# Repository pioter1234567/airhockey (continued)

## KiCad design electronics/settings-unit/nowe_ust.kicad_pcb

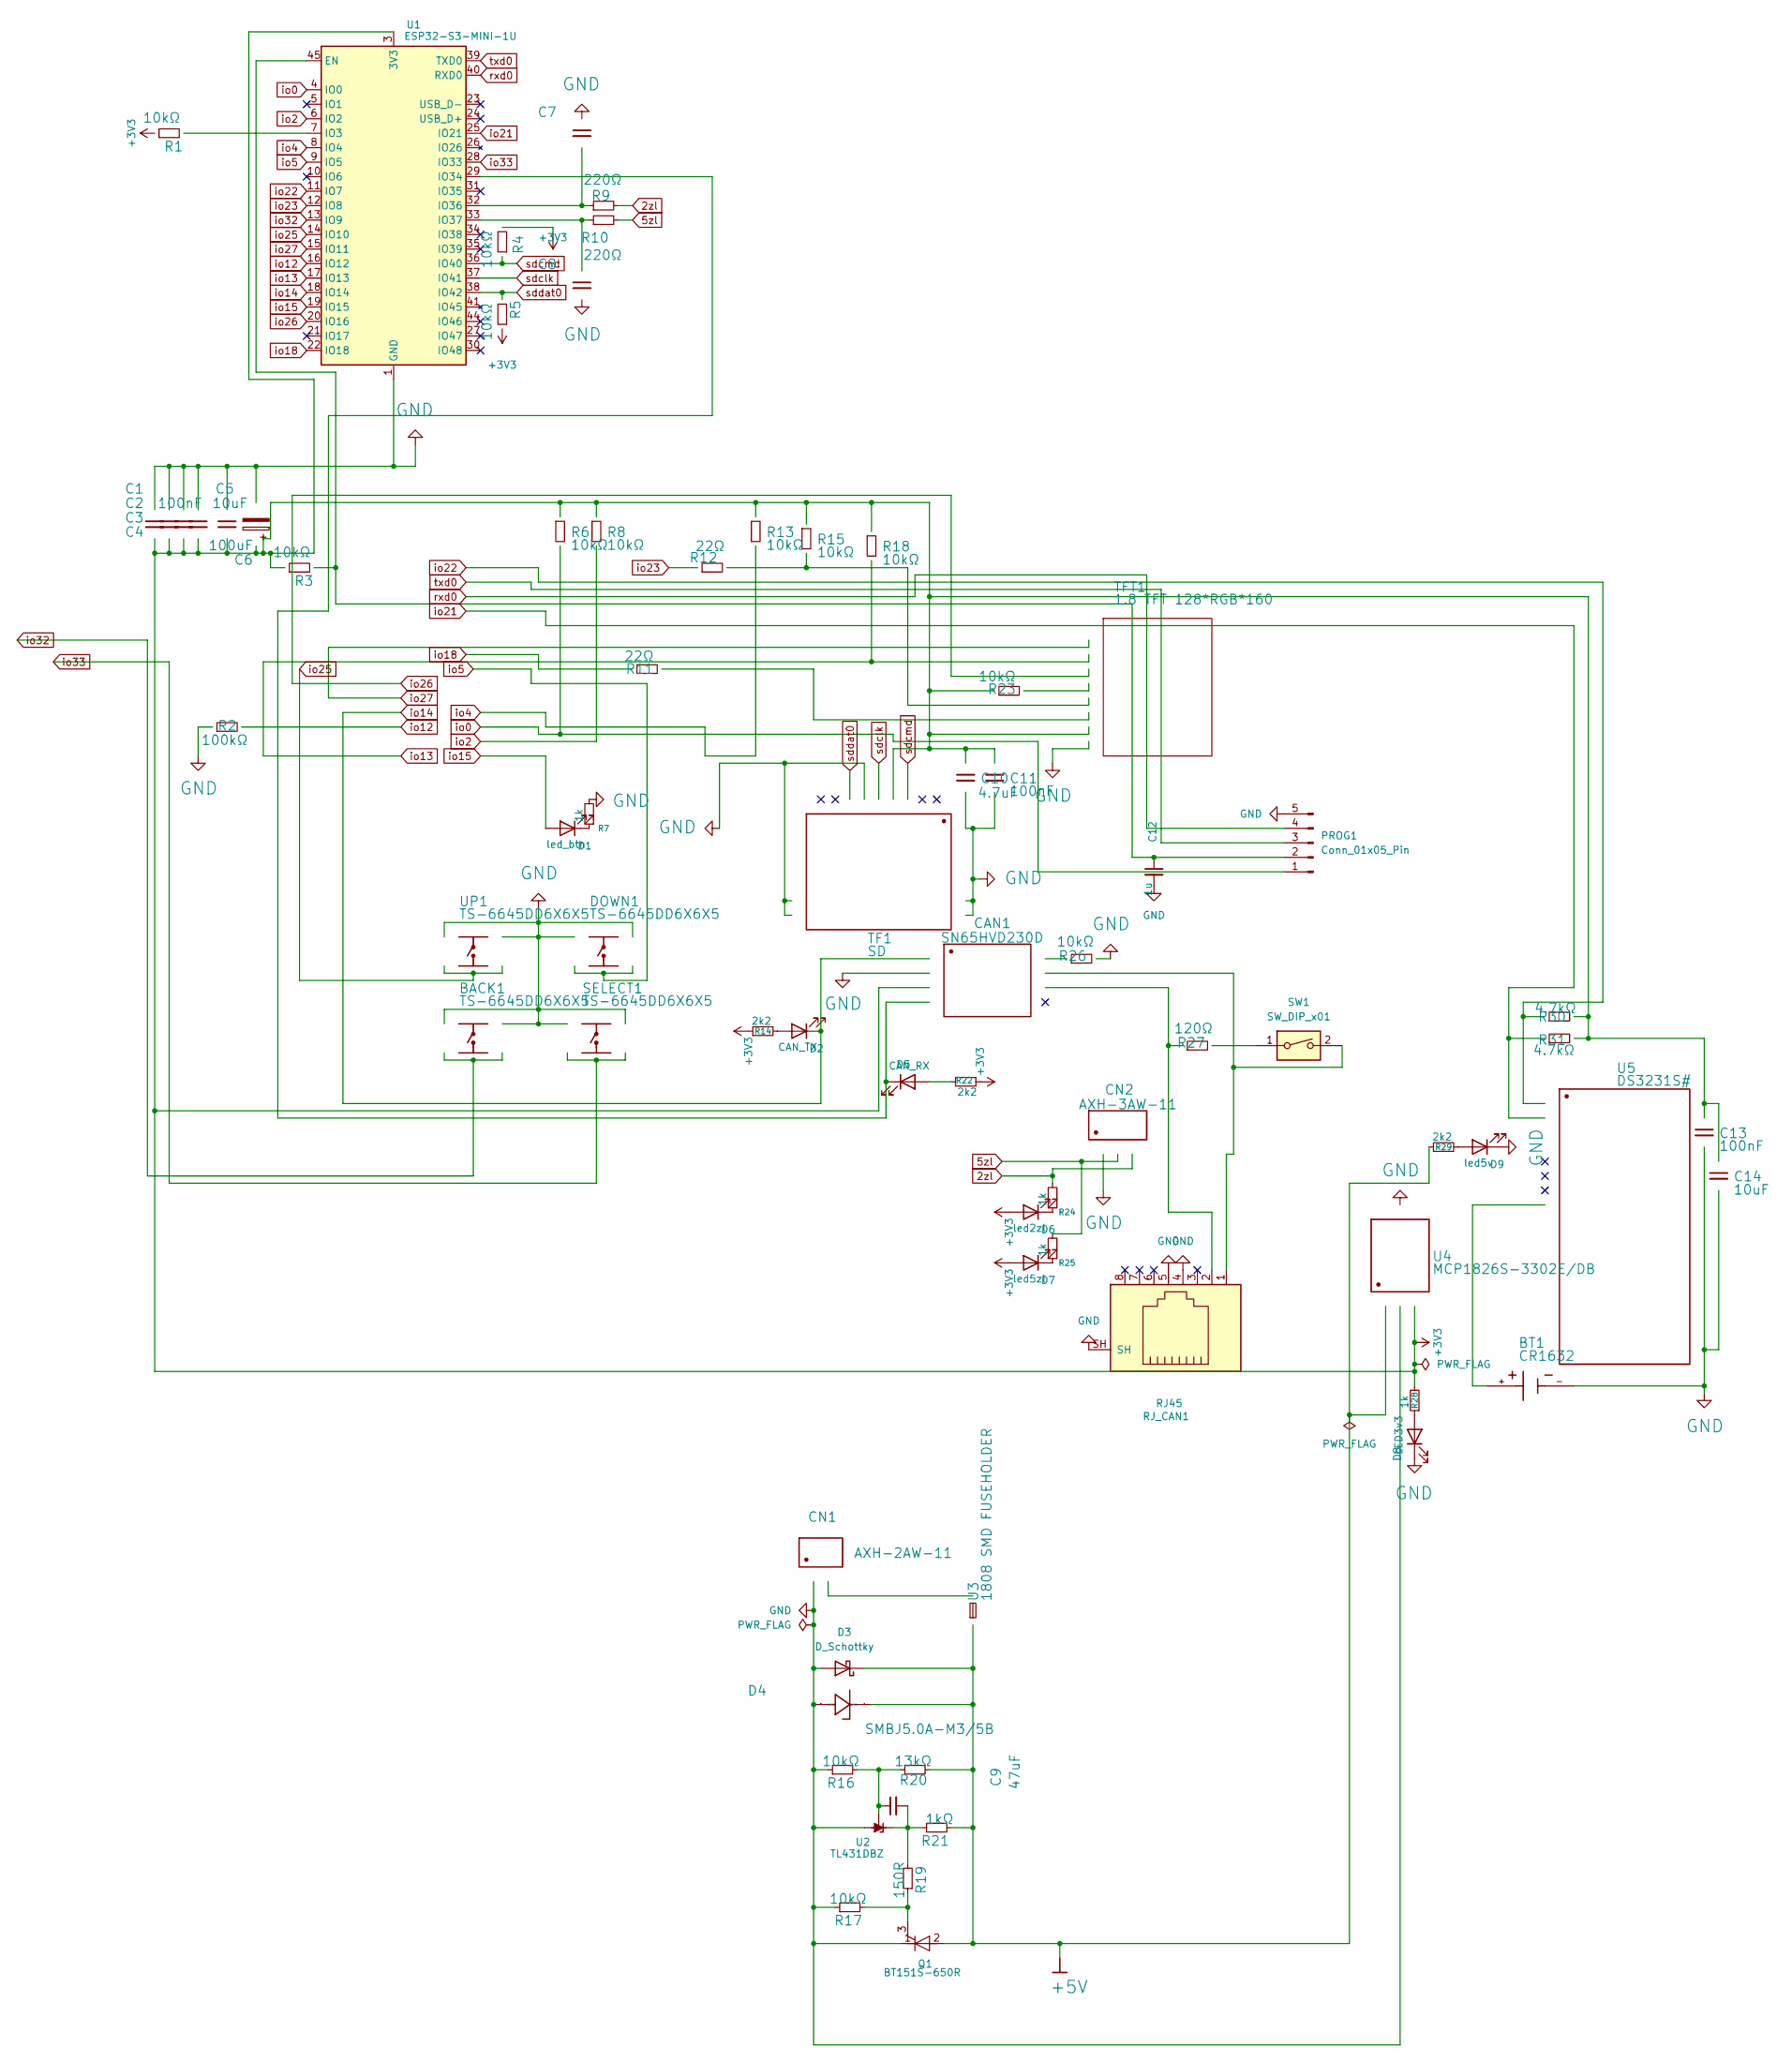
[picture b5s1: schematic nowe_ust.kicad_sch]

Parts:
BACK1: TS-6645DD6X6X5; SW_PUSH_6mm_H13mm; Manufacturer Part TS-6645DD6x6x5
BT1: CR1632; BAT_BU1632SM-JJ-GTR; Manufacturer Part XDBS-CR2032-9
C1, C2, C3, C4, C7, C8, C11, C13: 100nF; C_0805_2012Metric_Pad1.18x1.45mm_HandSolder; Manufacturer Part 0805B104K160CT-C
C5: 10uF; C_0805_2012Metric_Pad1.18x1.45mm_HandSolder; Manufacturer Part 0805ZD106KAT2A
C6: 100uF; CP_Elec_5x5.3; Manufacturer Part RVT100UF10V67RV0036
C9: 47uF; C_0805_2012Metric_Pad1.18x1.45mm_HandSolder; Manufacturer Part CGA0805X7R106K100MT
C10: 4.7uF; C_0805_2012Metric_Pad1.18x1.45mm_HandSolder; Manufacturer Part TCC0805X5R475M500FT
C12: 1u; C_0805_2012Metric
C14: 10uF; C_0805_2012Metric_Pad1.18x1.45mm_HandSolder; Manufacturer Part CGA0805X7R106K100MT
CAN1: SN65HVD230D; SOIC127P599X175-8N; Manufacturer Part SN65HVD230D
CN1: AXH-2AW-11; JST_XH_S2B-XH-A-1_1x02_P2.50mm_Horizontal; Manufacturer Part AXH-2AW-11
CN2: AXH-3AW-11; JST_PH_S3B-PH-K_1x03_P2.00mm_Horizontal; Manufacturer Part AXH-3AW-11
D1: led_btn; LED_0805_2012Metric
D2: CAN_TX; LED_0805_2012Metric
D3: D_Schottky; D_SMA
D4: SMBJ5.0A-M3/5B; D_SMB; Manufacturer Part SMBJ5.0A-M3/5B
D5: CAN_RX; LED_0805_2012Metric
D6: led2zl; LED_0805_2012Metric
D7: led5zl; LED_0805_2012Metric
D8: LED3v3; LED_0805_2012Metric
D9: led5v; LED_0805_2012Metric
DOWN1: TS-6645DD6X6X5; SW_PUSH_6mm_H13mm; Manufacturer Part TS-6645DD6x6x5
PROG1: Conn_01x05_Pin; JST_SH_BM05B-SRSS-TB_1x05-1MP_P1.00mm_Vertical
Q1: BT151S-650R; IC_BT136S-600E_118
R1, R3, R4, R5, R6, R8, R13, R15, R18: 10kΩ; R_0805_2012Metric; Manufacturer Part RCC080510K0FKEA
R2: 100kΩ; R_0805_2012Metric; Manufacturer Part APC0603B100KN
R7, R24, R25, R28: 1k; R_0805_2012Metric
R9, R10: 220Ω; R_0805_2012Metric; Manufacturer Part SC0805F22R0F4ANRH
R11, R12: 22Ω; R_0805_2012Metric; Manufacturer Part SC0805F22R0F4ANRH
R14, R22, R29: 2k2; R_0805_2012Metric
R16, R17: 10kΩ; R_0805_2012Metric; Manufacturer Part RMC08054.7K1%N
R19: 150R; R_0805_2012Metric; Manufacturer Part RMC08054.7K1%N
R20: 13kΩ; R_0805_2012Metric; Manufacturer Part RMC08054.7K1%N
R21: 1kΩ; R_0805_2012Metric; Manufacturer Part RMC08054.7K1%N
R23, R26: 10kΩ; R_0805_2012Metric; Manufacturer Part RT0603LRA0710KL
R27: 120Ω; R_0805_2012Metric; Manufacturer Part 0603SAJ0121T5E
R30, R31: 4.7kΩ; R_0805_2012Metric; Manufacturer Part RMC08054.7K1%N
RJ_CAN1: RJ45; RJ45_Amphenol_RJHSE5380
SELECT1: TS-6645DD6X6X5; SW_PUSH_6mm_H13mm; Manufacturer Part TS-6645DD6x6x5
SW1: SW_DIP_x01; SW_DIP_SPSTx01_Slide_6.7x4.1mm_W7.62mm_P2.54mm_LowProfile
TF1: SD; CUI_MSD-4-A; Manufacturer Part SD
TFT1: 1.8 TFT 128*RGB*160; TFT 1.8 No card No touch; Manufacturer Part 1.8 TFT 128*RGB*160
U1: ESP32-S3-MINI-1U; ESP32-S2-MINI-1U
U2: TL431DBZ; SOT-23
U3: 1808 SMD FUSEHOLDER; FUSE_1808; Manufacturer Part 1808 SMD Fuseholder
U4: MCP1826S-3302E/DB; MCP1826S-5002EDB; Manufacturer Part MCP1826S-3302E/DB
U5: DS3231S#; DS3231SN; Manufacturer Part DS3231S#
UP1: TS-6645DD6X6X5; SW_PUSH_6mm_H13mm; Manufacturer Part TS-6645DD6x6x5

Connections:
2zl: CN2.3 (2ZL), R9.2, R24.2
5zl: CN2.2 (5ZL), R10.2, R25.2
+3V3: C1.2, C2.2, C3.2, C4.2, C5.2, C6.1, C10.1, C11.1, C13.1, C14.1, CAN1.3 (VCC), D6.2 (A), D7.2 (A), R1.1, R3.1, R4.2, R5.1, R6.1, R8.1, R13.1, R14.1, R15.1, R18.1, R22.1, R23.1, R28.2, R30.2, R31.2, TF1.4 (VDD), TFT1.2 (VCC), U1.3 (3V3), U4.3 (VOUT), U5.2 (VCC)
+5V: D3.1 (K), D4.2 (K), Q1.2 (A), R20.2, R21.2, R29.1, U3.1, U4.1 (VIN)
unnamed: CAN1.7 (CANH), RJ_CAN1.1, SW1.2
unnamed: CAN1.6 (CANL), R27.1, RJ_CAN1.2
unnamed: CAN1.4 (R), D5.1 (K), U1.29 (IO34)
unnamed: CAN1.8 (RS), R26.1
unnamed: CN1.2 (5V), U3.2
unnamed: D1.1 (K), R7.1
unnamed: D2.2 (A), R14.2
unnamed: D5.2 (A), R22.2
unnamed: D6.1 (K), R24.1
unnamed: D7.1 (K), R25.1
unnamed: D8.2 (A), R28.1
unnamed: D9.2 (A), R29.2
unnamed: C12.1, PROG1.2, R3.2, U1.45 (EN)
unnamed: Q1.3 (G), R17.2, R19.1
unnamed: R27.2, SW1.1
unnamed: R23.2, TFT1.5 (RES)
unnamed: R11.2, TFT1.3 (SCK)
unnamed: R12.2, R15.2, TFT1.4 (SDA)
unnamed: R1.2, U1.7 (IO3)
unnamed: C7.2, R9.1, U1.32 (IO36)
unnamed: C8.1, R10.1, U1.33 (IO37)
unnamed: C9.2, R19.2, R21.1, U2.1 (K)
unnamed: C9.1, R16.2, R20.1, U2.2 (REF)
unnamed: BT1.+, U5.14 (VBAT)
io0: PROG1.1, R6.2, U1.4 (IO0)
io2: R8.2, U1.6 (IO2)
io4: R13.2, U1.8 (IO4)
io5: DOWN1.2 (3), U1.9 (IO5)
io12: R2.2, U1.16 (IO12)
io13: R18.2, TFT1.7 (CS), U1.17 (IO13)
io14: CAN1.1 (D), D2.1 (K), U1.18 (IO14)
io15: D1.2 (A), U1.19 (IO15)
io18: R11.1, U1.22 (IO18)
io21: R31.1, U1.25 (IO21), U5.15 (SDA)
io22: R30.1, U1.11 (IO7), U5.16 (SCL)
io23: R12.1, U1.12 (IO8)
io25: U1.14 (IO10), UP1.2 (3)
io26: TFT1.6 (DC), U1.20 (IO16)
io27: TFT1.8 (BL), U1.15 (IO11)
io32: BACK1.2 (3), U1.13 (IO9)
io33: SELECT1.2 (3), U1.28 (IO33)
rxd0: PROG1.4, U1.40 (RXD0)
sdclk: TF1.5 (CLK), U1.37 (IO41)
sdcmd: R4.1, TF1.3 (CMD), U1.36 (IO40)
sddat0: R5.2, TF1.7 (DAT0), U1.38 (IO42)
txd0: PROG1.3, U1.39 (TXD0)

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
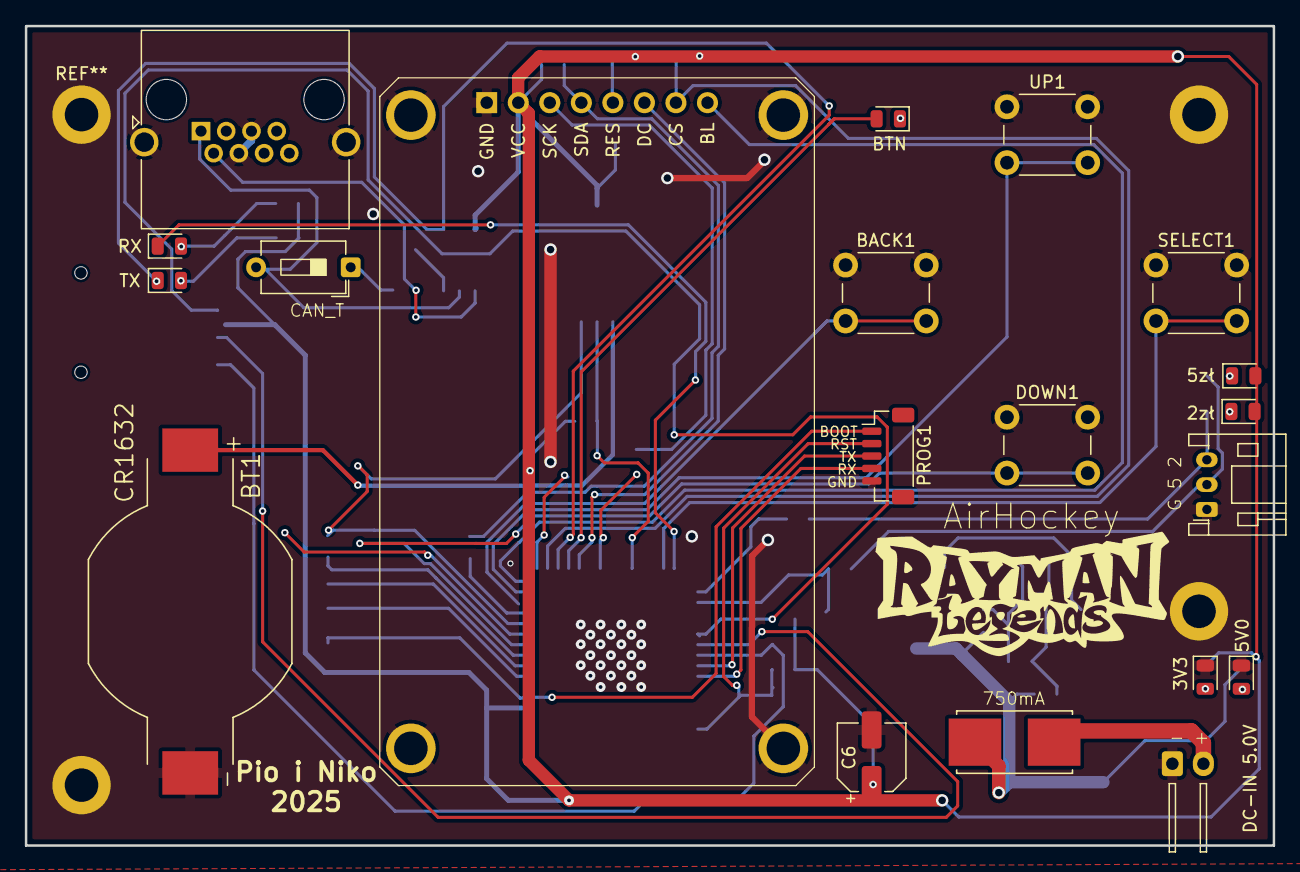
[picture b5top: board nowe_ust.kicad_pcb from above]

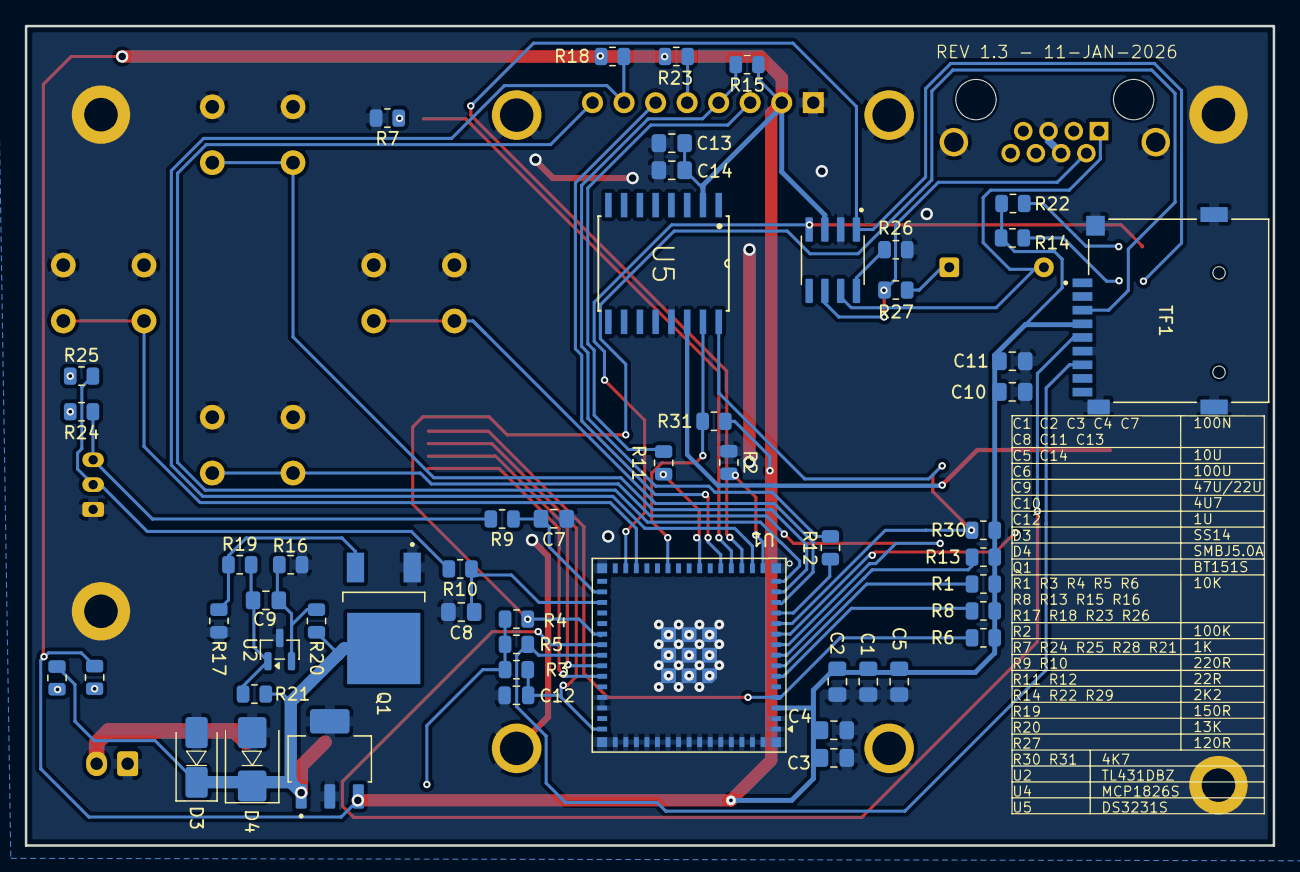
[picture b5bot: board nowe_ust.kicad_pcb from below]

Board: 2 copper layers, 100.5 x 66.0 mm, 73 parts (53 on the bottom side), 51 nets.

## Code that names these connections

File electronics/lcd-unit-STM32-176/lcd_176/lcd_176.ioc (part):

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Mcu.Name=STM32H743IITx
Mcu.Package=LQFP176
Mcu.UserName=STM32H743IITx
PA1.Mode=RGB888
PA1.Signal=LTDC_R2
PA10.Mode=RGB888
PA10.Signal=LTDC_B1
PA11.Mode=FDCAN_Activate
PA11.Signal=FDCAN1_RX
PA12.Mode=FDCAN_Activate
PA12.Signal=FDCAN1_TX
PA2.Mode=RGB888
PA2.Signal=LTDC_R1
PA3.Mode=RGB888
PA3.Signal=LTDC_B2
PA5.Mode=RGB888
PA5.Signal=LTDC_R4
PA6.Mode=RGB888
PA6.Signal=LTDC_G2
PA7.Signal=S_TIM14_CH1
PA8.Mode=RGB888
PA8.Signal=LTDC_B3
PB0.Mode=RGB888
PB0.Signal=LTDC_R3
PB1.Mode=RGB888
PB1.Signal=LTDC_R6
PB10.Mode=I2C
PB10.Signal=I2C2_SCL
PB11.Mode=RGB888
PB11.Signal=LTDC_G5
PB6.Mode=I2C
PB6.Signal=I2C1_SCL
PB7.Mode=I2C
PB7.Signal=I2C1_SDA
PB8.Mode=RGB888
PB8.Signal=LTDC_B6
PB9.Mode=RGB888
PB9.Signal=LTDC_B7
PC0.Signal=FMC_SDNWE
PC10.Mode=SD_4_bits_Wide_bus
PC10.Signal=SDMMC1_D2
PC11.Mode=SD_4_bits_Wide_bus
PC11.Signal=SDMMC1_D3
PC12.Mode=SD_4_bits_Wide_bus
PC12.Signal=SDMMC1_CK
PC2_C.Mode=SdramChipSelect1_1
PC2_C.Signal=FMC_SDNE0
PC3_C.Mode=SdramChipSelect1_1
PC3_C.Signal=FMC_SDCKE0
PC8.Mode=SD_4_bits_Wide_bus
PC8.Signal=SDMMC1_D0
PC9.Mode=SD_4_bits_Wide_bus
PC9.Signal=SDMMC1_D1
PD0.Signal=FMC_D2_DA2
PD1.Signal=FMC_D3_DA3
PD10.Signal=FMC_D15_DA15
PD14.Signal=FMC_D0_DA0
PD15.Signal=FMC_D1_DA1
PD2.Mode=SD_4_bits_Wide_bus
PD2.Signal=SDMMC1_CMD
PD8.Signal=FMC_D13_DA13
PD9.Signal=FMC_D14_DA14
PE0.Signal=FMC_NBL0
PE1.Signal=FMC_NBL1
PE10.Signal=FMC_D7_DA7
PE11.Signal=FMC_D8_DA8
PE12.Signal=FMC_D9_DA9
PE13.Signal=FMC_D10_DA10
PE14.Signal=FMC_D11_DA11
PE15.Signal=FMC_D12_DA12
PE4.Mode=RGB888
PE4.Signal=LTDC_B0
PE5.Mode=RGB888
PE5.Signal=LTDC_G0
PE6.Mode=RGB888
PE6.Signal=LTDC_G1
PE7.Signal=FMC_D4_DA4
PE8.Signal=FMC_D5_DA5
PE9.Signal=FMC_D6_DA6
PF0.Signal=FMC_A0
PF1.Signal=FMC_A1
PF10.Mode=RGB888
PF10.Signal=LTDC_DE
PF11.Signal=FMC_SDNRAS
PF12.Signal=FMC_A6
PF13.Signal=FMC_A7
PF14.Signal=FMC_A8
PF15.Signal=FMC_A9
PF2.Signal=FMC_A2
PF3.Signal=FMC_A3
PF4.Signal=FMC_A4
PF5.Signal=FMC_A5
PF6.GPIOParameters=GPIO_Label
PF6.GPIO_Label=lcd_on_high
PF6.Signal=GPIO_Output
PG0.Signal=FMC_A10
PG1.Signal=FMC_A11
PG12.Mode=RGB888
PG12.Signal=LTDC_B4
PG15.Signal=FMC_SDNCAS
PG4.Signal=FMC_A14_BA0
PG5.Signal=FMC_A15_BA1
PG6.Mode=RGB888
PG6.Signal=LTDC_R7
PG7.Mode=RGB888
PG7.Signal=LTDC_CLK
PG8.Signal=FMC_SDCLK
PH11.Mode=RGB888
PH11.Signal=LTDC_R5
PH14.Mode=RGB888
PH14.Signal=LTDC_G3
PH2.Mode=RGB888
PH2.Signal=LTDC_R0
PH4.Mode=RGB888
PH4.Signal=LTDC_G4
PH5.Mode=I2C
PH5.Signal=I2C2_SDA
PI10.Mode=RGB888
PI10.Signal=LTDC_HSYNC
PI11.Mode=RGB888
PI11.Signal=LTDC_G6
PI2.Mode=RGB888
PI2.Signal=LTDC_G7
PI5.Mode=RGB888
PI5.Signal=LTDC_B5
PI9.Mode=RGB888
PI9.Signal=LTDC_VSYNC
RCC.SYSCLKFreq_VALUE=64000000
board=custom

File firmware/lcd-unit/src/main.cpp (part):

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
//SD

#define SD_CS   34   // SCS
#define SD_MOSI 35   // SDI
#define SD_MISO 37   // SDO
#define SD_SCK  36   // CLK

TwoWire I2C2 = TwoWire(1); // Wire1
Adafruit_SH1106G oled1(128, 64, &Wire, -1);
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
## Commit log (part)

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2026-03-13 Initial backup
2026-03-13 Add gitignore for build files
2026-03-13 Ignore KiCad backups and autosaves
2026-03-13 Assets added - SD cards for devices
2026-03-16 Auto goal calibration added
2026-03-17 lcd-unit added
2026-03-17 fix: correct theme mapping in music and full rounds
2026-03-19 lcd-unit games backgrounds complete; transition fixed between screens
2026-03-19 jpg to bin converter now converts the whole catalogue
2026-03-20 goal animations test moved to anims.cpp moved display params to display.h
2026-03-21 goal animation logic for both sides; 3d models added
2026-03-21 points display fix; end match points added
2026-03-21 all character animations added
2026-03-21 duplicates removed
2026-03-23 blinking score added; duplicated game over fixed
2026-03-28 lamp animation fix
2026-03-29 postGame bug fixed, missing anims added, converter fseq fixed
2026-03-29 Time autochange added - daylight savings
2026-03-29 Turn ON lamp added to setting unit
2026-03-29 Loop in main-unit tidied, priority given to manual handle of lamp
2026-03-29 all animations done
2026-04-10 lamp fans control added; uv boost anims added; ambiente light timeout fixed
2026-04-10 test
2026-04-11 fail safe added to lamp fans
2026-04-11 UV control fixed
2026-04-11 some photos
2026-06-02 Ambiente lighting draft, song order fixet for music rounds, many others
2026-06-02 Ambiente all songs added
2026-06-09 RTC corrected
2026-06-12 Goal animations added, fixed BIN animation glitch after goal
2026-06-22 Goal lightning
2026-06-22 lcd ANIMs fixed - previous game ghost
2026-06-22 sound effects between rounds and at the end
2026-06-22 sound effects between rounds and at the end, fixed goal sides
